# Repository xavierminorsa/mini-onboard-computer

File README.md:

# Mini-OBC

**Author:** Xavier Minorsa  
**Tool:** KiCad 9.0.6

Licensed under CERN-OHL-S-2.0

---

This README details the hardware design choices and development of the Mini On-Board Computer. The objective is to design a reliable, low-power Mini-OBC that includes a MCU, memory module, gyroscope, etc.

The philosophy adopted for this Mini-OBC project highly focuses on power-efficiency, by selecting low-power components like an MCU from the STM32L family.

---

## Table of Contents

- [Glossary](#glossary)
- [Choosing an MCU](#choosing-an-mcu)
- [Choosing a Storage Module](#choosing-a-storage-module)
- [Assembly & Schematics](#assembly--schematics)
  - [MCU](#mcu)
  - [LSE Crystal](#lse-crystal)
  - [ST-LINK V2 Connector](#st-link-v2-connector)
  - [Gyroscope ASM330LHHX](#gyroscope-asm330lhhx)
  - [Power Input](#power-input)
  - [NAND Flash Memory Module](#nand-flash-memory-module)
- [PCB & 3D Renders](#pcb--3d-renders)
- [References](#references)

---

## Glossary

| Acronym | Definition |
|---------|------------|
| CS | Chip Select |
| DRC | Design Rule Check |
| ECC | Error Correction Code |
| FPU | Floating-Point Unit |
| GPIO | General-Purpose Input/Output |
| I²C | Inter-Integrated Circuit |
| I/O | Input/Output |
| JTAG | Joint Test Action Group |
| LSE | Low-Speed External |
| MCU | Microcontroller Unit |
| MOSFET | Metal-Oxide-Semiconductor Field-Effect Transistor |
| NAND | Not AND (Flash Memory) |
| NOR | Not OR (Flash Memory) |
| NRST | System Reset (Active Low) |
| OBC | On-Board Computer |
| PCB | Printed Circuit Board |
| RAM | Random-Access Memory |
| RTC | Real-Time Clock |
| RTOS | Real-Time Operating System |
| SMPS | Switched-Mode Power Supply |
| SPI | Serial Peripheral Interface |
| SRAM | Static Random-Access Memory |
| SWCLK | Serial Wire Clock |
| SWD | Serial Wire Debug |
| SWDIO | Serial Wire Data Input/Output |
| UART | Universal Asynchronous Receiver-Transmitter |
| USART | Universal Synchronous/Asynchronous Receiver-Transmitter |
| VCC | Voltage Common Collector |

---

## Choosing an MCU

Choosing the right MCU consists in considering the limited resources and the rough environment that the satellite will operate in. The following selection was based on a hierarchy of requirements:

- **Power efficiency:** Power efficiency is arguably the most critical parameter. The MCU must offer the lowest possible power consumption in Run mode and low-power modes to save battery life during orbital eclipses.
- **Memory management:** Memory management must provide sufficient capacity to host the chosen RTOS, flight software, and data buffers. And at the same time utilizing the internal SRAM to avoid the need for external RAM chips for this project alone (however, in a real CubeSat mission, it is strongly recommended to include an external RAM chip).
- **Processing Capability**
- **Number of GPIO ports and Communication interfaces included**

My first choice was initially the STM32F401, it has been used in CubeSat projects before [[1]](#references), therefore a solid candidate. However, since 64 KB won't be enough to run RTOS entirely in the MCU's SRAM, 64 KB of SRAM is very limited for such task. With that obstacle in mind, I meticulously searched the STMicroelectronics' catalog, while prioritizing low-power and high SRAM density. This process along with another CubeSat project I found that used a low-power MCU [[2]](#references), resulted in the selection of the superior STM32L4P5, an STM32L is slightly more powerful and power efficient variant.

### MCU Comparative Analysis

| Feature | STM32L4P5 (Selected) [[3]](#references) | STM32L496 (Candidate B) [[4]](#references) | STM32F401 (Baseline) [[5]](#references) |
|---------|----------------------------------------|-------------------------------------------|----------------------------------------|
| Architecture Focus | Ultra-Low-Power & Performance | Ultra-Low-Power | Dynamic Efficiency (Standard) |
| Core | Arm® Cortex®-M4 + FPU | Arm® Cortex®-M4 + FPU | Arm® Cortex®-M4 + FPU |
| Max Frequency | 120 MHz | 80 MHz | 84 MHz |
| Flash Memory | Up to 1 MB | Up to 1 MB | Up to 256 KB |
| Internal SRAM | 320 KB | 320 KB | 64 KB |
| Active Consumption (Run) | 41 µA/MHz (SMPS mode) | 37 µA/MHz (SMPS mode) | 128 µA/MHz |
| Sleep Consumption | 42 nA (Standby mode) | 108 nA (Standby mode) | 42 µA (Stop mode) |
| Max GPIOs (I/O) | Up to 136 (depends on package) | Up to 136 (depends on package) | Up to 81 (depends on package) |
| SPI Interfaces | 3 | 3 | 4 |
| UART/USART Interfaces | 6 (5x USART + 1x LPUART) | 6 (5x USART + 1x LPUART) | 3 |
| I2C Interfaces | 4 | 4 | 3 |

In this decision, the STM32F401 was initially discarded. Even though it is low cost, its limiting SRAM (64 KB) prevented the adoption of our Integrated Architecture, which would require an external RAM. The true trade-off starts when focusing on the ultra-low-power MCUs, the STM32L496 that was already used in a CubeSat project, and the STM32L4P5. Both having 320 KB of SRAM, great for isolating the FreeRTOS. However, the STM32L4P5 was selected because it offers a vastly superior performance over the STM32L496.

---

## Choosing a Storage Module

The storage module should act like a CubeSat's secondary "hard drive" responsible to store the log data related to critical telemetry, orbital altitude, etc. The following selection was based on a hierarchy of requirements:

- **Power Efficiency**
- **Storage capability**
- **Endurance and Reliability**
- **Serial communication interface used**

It was selected two industry-standard 2Gb SPI NAND Flash modules: the Winbond W25N02KV and the Micron MT29F2G01AB (that has been used in a CubeSat mission [[6]](#references)), both sharing an identical physical footprint (8x6 mm, 8-pins).

The reason NAND flash memory was selected for this project is because NAND Flashes offer high storage density, are non-volatile, writing/erasing speeds are very fast, and they are incredibly durable. Other flash memories like SD Card were considered, which offer way more flexibility, but they require a mechanical connector — in a space environment, intense vibrations can happen any time, which can cause mechanical contact failures. On the other hand, NOR flash memories are a good contender as they offer fast read speeds, but NAND is faster in erasing data and offers higher density of storage.

### NAND Flash Comparative Analysis

| Parameter | Winbond W25N02KV (Selected) [[7]](#references) | Micron MT29F2G01AB (Baseline) [[8]](#references) |
|-----------|-----------------------------------------------|--------------------------------------------------|
| Capacity & Voltage | 2Gb (256 MB) / 2.7V to 3.6V | 2Gb (256 MB) / 2.7V to 3.6V |
| Clock Speed (SPI) | 104 MHz | 133 MHz |
| Erase Cycles (Endurance) | 100,000 cycles | 100,000 cycles |
| Sleep Consumption | 1 µA (Deep Power-Down) | ~10 to 50 µA (Standard Standby) |
| Active Read Current | 25 mA | 25 mA |
| Error Correction (ECC) | Internal (8-bit) | Internal (8-bit) |

Overall both memory modules are very capable and similar in terms of performance and even form factor (sharing the same footprint). In this decision, the Winbond W25N02KV was selected as the secondary storage module for the OBC due to sharing similar performance — despite the W25N02KV's clock speed being slightly inferior to the MT29F2G01AB, its superior sleep consumption highly overlaps the small inconvenience of having less clock speed.

---

## Assembly & Schematics

### MCU

A decoupling capacitor was added for each power port the MCU has, plus a 4.7 µF decoupler required by the datasheet. A switch was also added in the boot line to enable/disable boot mode.

STM32CubeMX was used to help check and assign the correct pins for each connection. Although this could be done by checking the datasheet, the STM32CubeMX gives a practical overview that allows you to interact with each pin and check what each pin does.

---

### LSE Crystal

An LSE (Low-Speed External) Crystal was implemented to act as an external RTC for the OBC to provide an accurate, low-power clock source and timing functions. Although the MCU has an inbuilt RTC, the usage of an external RTC increases its reliability. The standard frequency is 32.768 kHz because it has a power of 2 (2¹⁵), allowing for easy division down to 1 Hz.

In order to calculate the capacitance of each capacitor, the following equation was used:

$$C_1 = C_2 = 2 \times (C_{\text{crystal}} - C_{\text{stray}})$$

Where $C_{\text{stray}}$ (stray capacitance) is typically 3 pF to 5 pF.

---

### ST-LINK V2 Connector

A header for ST-LINK V2 with Serial Wire Debug (SWD) interface was added to allow upload and real-time debugging between the MCU and the debugging device.

The board features a 10-pin header that provides the necessary connections. The pinout is compatible with standard ST-Link V2 and V3 programmers:

| Pin | Signal | Description |
|-----|--------|-------------|
| 1 | VCC (3.3V) | Power supply |
| 2 | SWDIO | Serial Wire Data I/O — bi-directional data line for communication between debugger and MCU |
| 3, 5, 9 | GND | Ground |
| 4 | SWCLK | Serial Wire Clock — driven by the ST-Link to synchronize data transfer |
| 10 | NRST | System Reset (Active Low) — allows the programmer to perform a hardware reset of the MCU |

The benefits of using the SWD protocol instead of JTAG are the reduced amount of necessary pins, simplified routing and the full debug capability — it allows full access to memory, registers, etc.

---

### Gyroscope ASM330LHHX

The ASM330LHHX was recommended for this project due to its reliability under high thermal conditions and resilience to vibrations. The gyroscope supports both I²C and SPI protocols, however it was configured to operate via SPI due to its superior transmission speed, reduced latency and signal integrity robustness. Mode 1 was adopted because additional external sensors weren't used to justify the usage of Mode 2. Decoupling capacitors were applied for each power source, following its datasheet's recommendation.

---

### Power Input

A power supply can be connected through J2, a 2-pin header supplying 3.3V and ground. Previously an inline diode reverse-polarity protection was considered; however, the forward voltage drops 0.7V when using this approach, violating minimum operating requirements of certain components. Therefore the inline diode was removed, and instead a P-Channel MOSFET [[9]](#references) was implemented to pass current with little loss of voltage. If the polarities connected are reversed, the MOSFET closes, blocking the reverse energy and preventing the board from burning — making it ideal for projects that prioritize power-saving.

---

### NAND Flash Memory Module

The memory module communicates with the MCU via SPI protocol. A pull-up resistor was added to the CS pin to prevent memory corruption from electrical noise. A single decoupler was added to the VCC pin as suggested by its datasheet.

---

## PCB & 3D Renders

---

## Good additions to be made

### Adding Probing pads
One of the suggestions given was to add probe test points to critical pins to help debug problems, such as with power pins, SPI's clock, CS, MISO/MOSI pins, I2C's Clock and data pins, etc...

---

## References

1. Ghatul, S., Chandra P., B., Jain, S., Nair, B. G., Babu, M., Mohan, R., Safonova, M., & Murthy, J. (2020). CubeOps: Development of an STM32 based on-board computer (OBC) for small satellites and CubeSat missions. In *Space Telescopes and Instrumentation 2020: Ultraviolet to Gamma Ray* (Vol. 11444, p. 1144476). SPIE.

2. RG SAT. (2020, July 5). *Building a CubeSat for less than $1000 — Part 3 — Avionics Schematic* [Video]. YouTube. https://www.youtube.com/watch?v=nSqU23qWrQA

3. STMicroelectronics. (2021). *STM32L4P5xx: Ultra-low-power Arm® Cortex®-M4 32-bit MCU+FPU, 150 DMIPS, up to 1-MB Flash memory, 320-KB SRAM, LCD-TFT, ext. SMPS* (DS12903 Rev 3).

4. STMicroelectronics. (2025). *STM32L496xx: Ultra-low-power Arm® Cortex®-M4 32-bit MCU+FPU, 100 DMIPS, up to 1 MB flash, 320 KB SRAM, USB OTG FS, audio, HASH, external SMPS* (DS11585 Rev 20).

5. STMicroelectronics. (2019). *STM32F401xB STM32F401xC: Arm® Cortex®-M4 32-bit MCU+FPU, 105 DMIPS, 256KB Flash / 64KB RAM, 11 TIMS, 1 ADC, 11 comm. interfaces* (DS9716 Rev 11).

6. Horbach, A. (2021). *Development of an on-board computer for a nanosatellite* [Master's thesis, University of Liège]. MatheO. http://hdl.handle.net/2268.2/11659

7. Winbond Electronics. (2021). *W25N02KVxxIR/U: 3V 2G-bit SLC QspiNAND Flash Memory with Dual/Quad SPI* (Rev. G).

8. Micron Technology. (2015). *2Gb 3.3V x1, x2, x4: SPI NAND Flash Memory* (Rev. F 09/16).

9. Afrotechmods. (2011, December 2). *How to protect circuits from reversed voltage polarity!* [Video]. YouTube. https://www.youtube.com/watch?v=IrB-FPcv1Dc

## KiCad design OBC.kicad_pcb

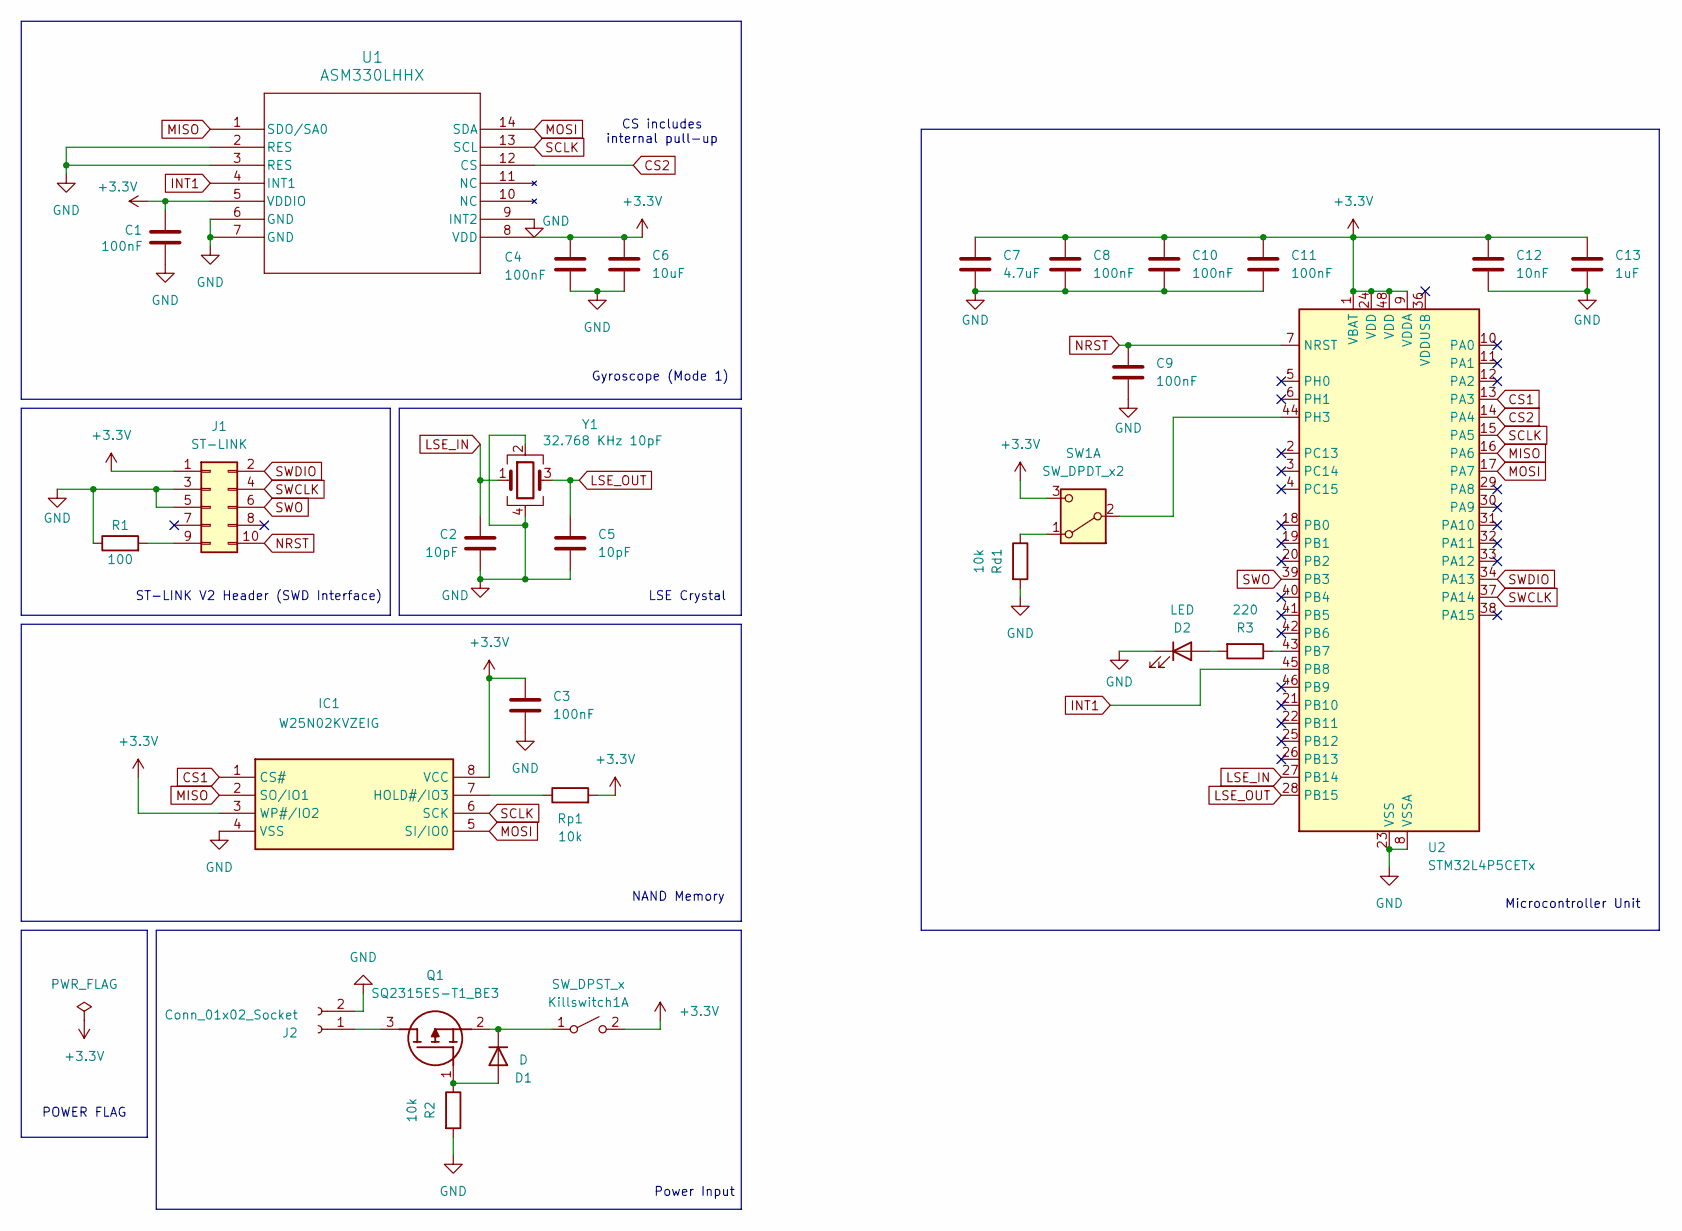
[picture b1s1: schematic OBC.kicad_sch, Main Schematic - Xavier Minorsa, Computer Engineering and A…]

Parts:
C1, C3, C4, C8, C9, C10, C11: 100nF; C_0603_1608Metric
C2, C5: 10pF; C_0603_1608Metric
C6: 10uF; C_0603_1608Metric
C7: 4.7uF; C_0603_1608Metric
C12: 10nF; C_0603_1608Metric
C13: 1uF; C_0603_1608Metric
D1: D; D_0603_1608Metric
D2: LED; LED_0603_1608Metric
IC1: W25N02KVZEIG; SON127P600X800X65-8N; Mouser Part Number 340-319922-REEL
J1: ST-LINK; PinHeader_2x05_P1.00mm_Vertical
J2: Conn_01x02_Socket; TerminalBlock_MaiXu_MX126-5.0-02P_1x02_P5.00mm
Killswitch1: SW_DPST_x; SW_DIP_SPSTx01_Slide_6.7x4.1mm_W7.62mm_P2.54mm_LowProfile
Q1: SQ2315ES-T1_BE3; SOT95P237X112-3N; Mouser Part Number 78-SQ2315ES-T1_BE3
R1: 100; R_0603_1608Metric
R2: 10k; R_0603_1608Metric
R3: 220; R_0603_1608Metric
Rd1: 10k; R_0603_1608Metric
Rp1: 10k; R_0603_1608Metric
SW1: SW_DPDT_x2; SW_MINI-SPDT-SW
U1: ASM330LHHX; LGA14_ASM330_STM-M
U2: STM32L4P5CETx; LQFP-48_7x7mm_P0.5mm
Y1: 32.768 KHz 10pF; Crystal_SMD_0603-4Pin_6.0x3.5mm

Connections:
+3.3V: C1.1, C3.1, C4.1, C6.1, C7.1, C8.1, C10.1, C11.1, C12.1, C13.1, IC1.3 (WP#/IO2), IC1.8 (VCC), J1.1, Killswitch1.2 (B), Rp1.2, SW1.3 (C), U1.5 (VDDIO), U1.8 (VDD), U2.1 (VBAT), U2.9 (VDDA), U2.24 (VDD), U2.48 (VDD)
CS1: IC1.1 (CS#), U2.13 (PA3)
CS2: U1.12 (CS), U2.14 (PA4)
GND: C1.2, C2.2, C3.2, C4.2, C5.2, C6.2, C7.2, C8.2, C9.2, C10.2, C11.2, C12.2, C13.2, D2.1 (K), IC1.4 (VSS), J1.3, J1.5, J2.2, R1.1, R2.2, Rd1.2, U1.2 (RES), U1.3 (RES), U1.6 (GND), U1.7 (GND), U1.9 (INT2), U2.8 (VSSA), U2.23 (VSS), U2.35 (VSS), U2.47 (VSS), Y1.2, Y1.4
INT1: U1.4 (INT1), U2.45 (PB8)
LSE_IN: C2.1, U2.27 (PB14), Y1.1
LSE_OUT: C5.1, U2.28 (PB15), Y1.3
MISO: IC1.2 (SO/IO1), U1.1 (SDO/SA0), U2.16 (PA6)
MOSI: IC1.5 (SI/IO0), U1.14 (SDA), U2.17 (PA7)
NRST: C9.1, J1.10, U2.7 (NRST)
unnamed: D1.2 (A), Q1.1 (G), R2.1
unnamed: D1.1 (K), Killswitch1.1 (A), Q1.2 (S)
unnamed: D2.2 (A), R3.2
unnamed: IC1.7 (HOLD#/IO3), Rp1.1
unnamed: J1.9, R1.2
unnamed: J2.1, Q1.3 (D)
unnamed: Rd1.1, SW1.1 (A)
unnamed: SW1.2 (B), U2.44 (PH3)
unnamed: R3.1, U2.43 (PB7)
SCLK: IC1.6 (SCK), U1.13 (SCL), U2.15 (PA5)
SWCLK: J1.4, U2.37 (PA14)
SWDIO: J1.2, U2.34 (PA13)
SWO: J1.6, U2.39 (PB3)

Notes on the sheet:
ST-LINK V2 Header (SWD Interface)
CS includes internal pull-up
POWER FLAG
LSE Crystal
Gyroscope (Mode 1)
Microcontroller Unit
NAND Memory
Power Input

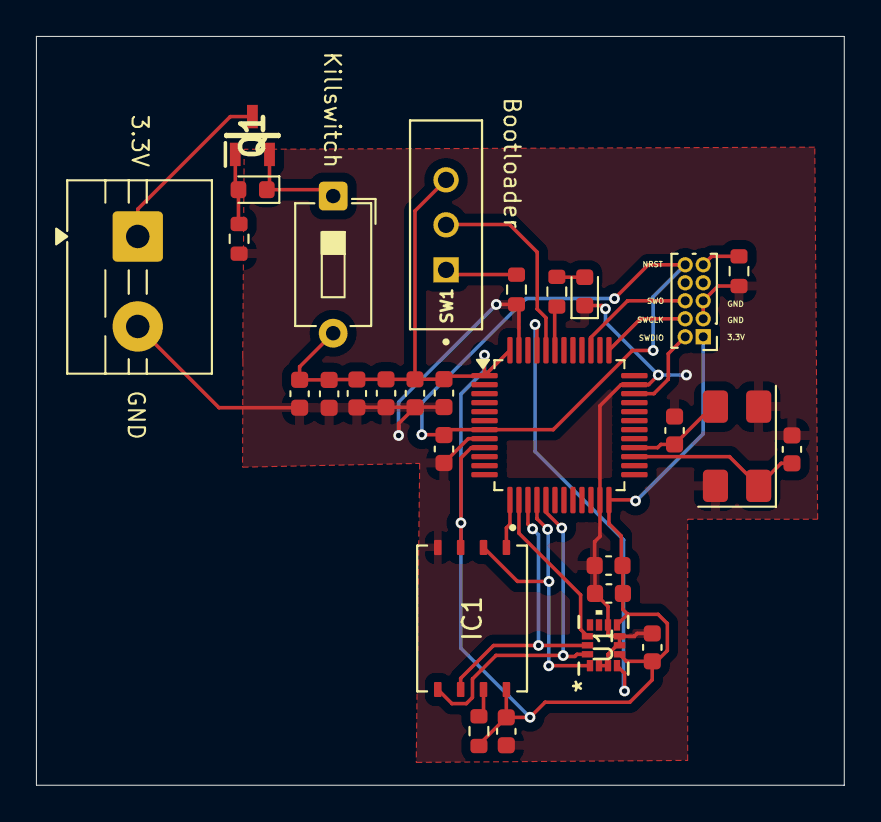
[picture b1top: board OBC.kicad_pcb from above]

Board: 2 copper layers, 44.9 x 41.6 mm, 29 parts (0 on the bottom side), 23 nets.

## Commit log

2026-05-03 Addition of KiCad Files
2026-05-03 Create LICENSE
